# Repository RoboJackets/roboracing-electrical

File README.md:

# RoboRacing Electrical
This is a repository for the RoboJackets' RoboRacing Electrical team.

## rigatoni
Contains current files associated with Rigatoni.

## archive
Contains old files no longer in use on the current robots.

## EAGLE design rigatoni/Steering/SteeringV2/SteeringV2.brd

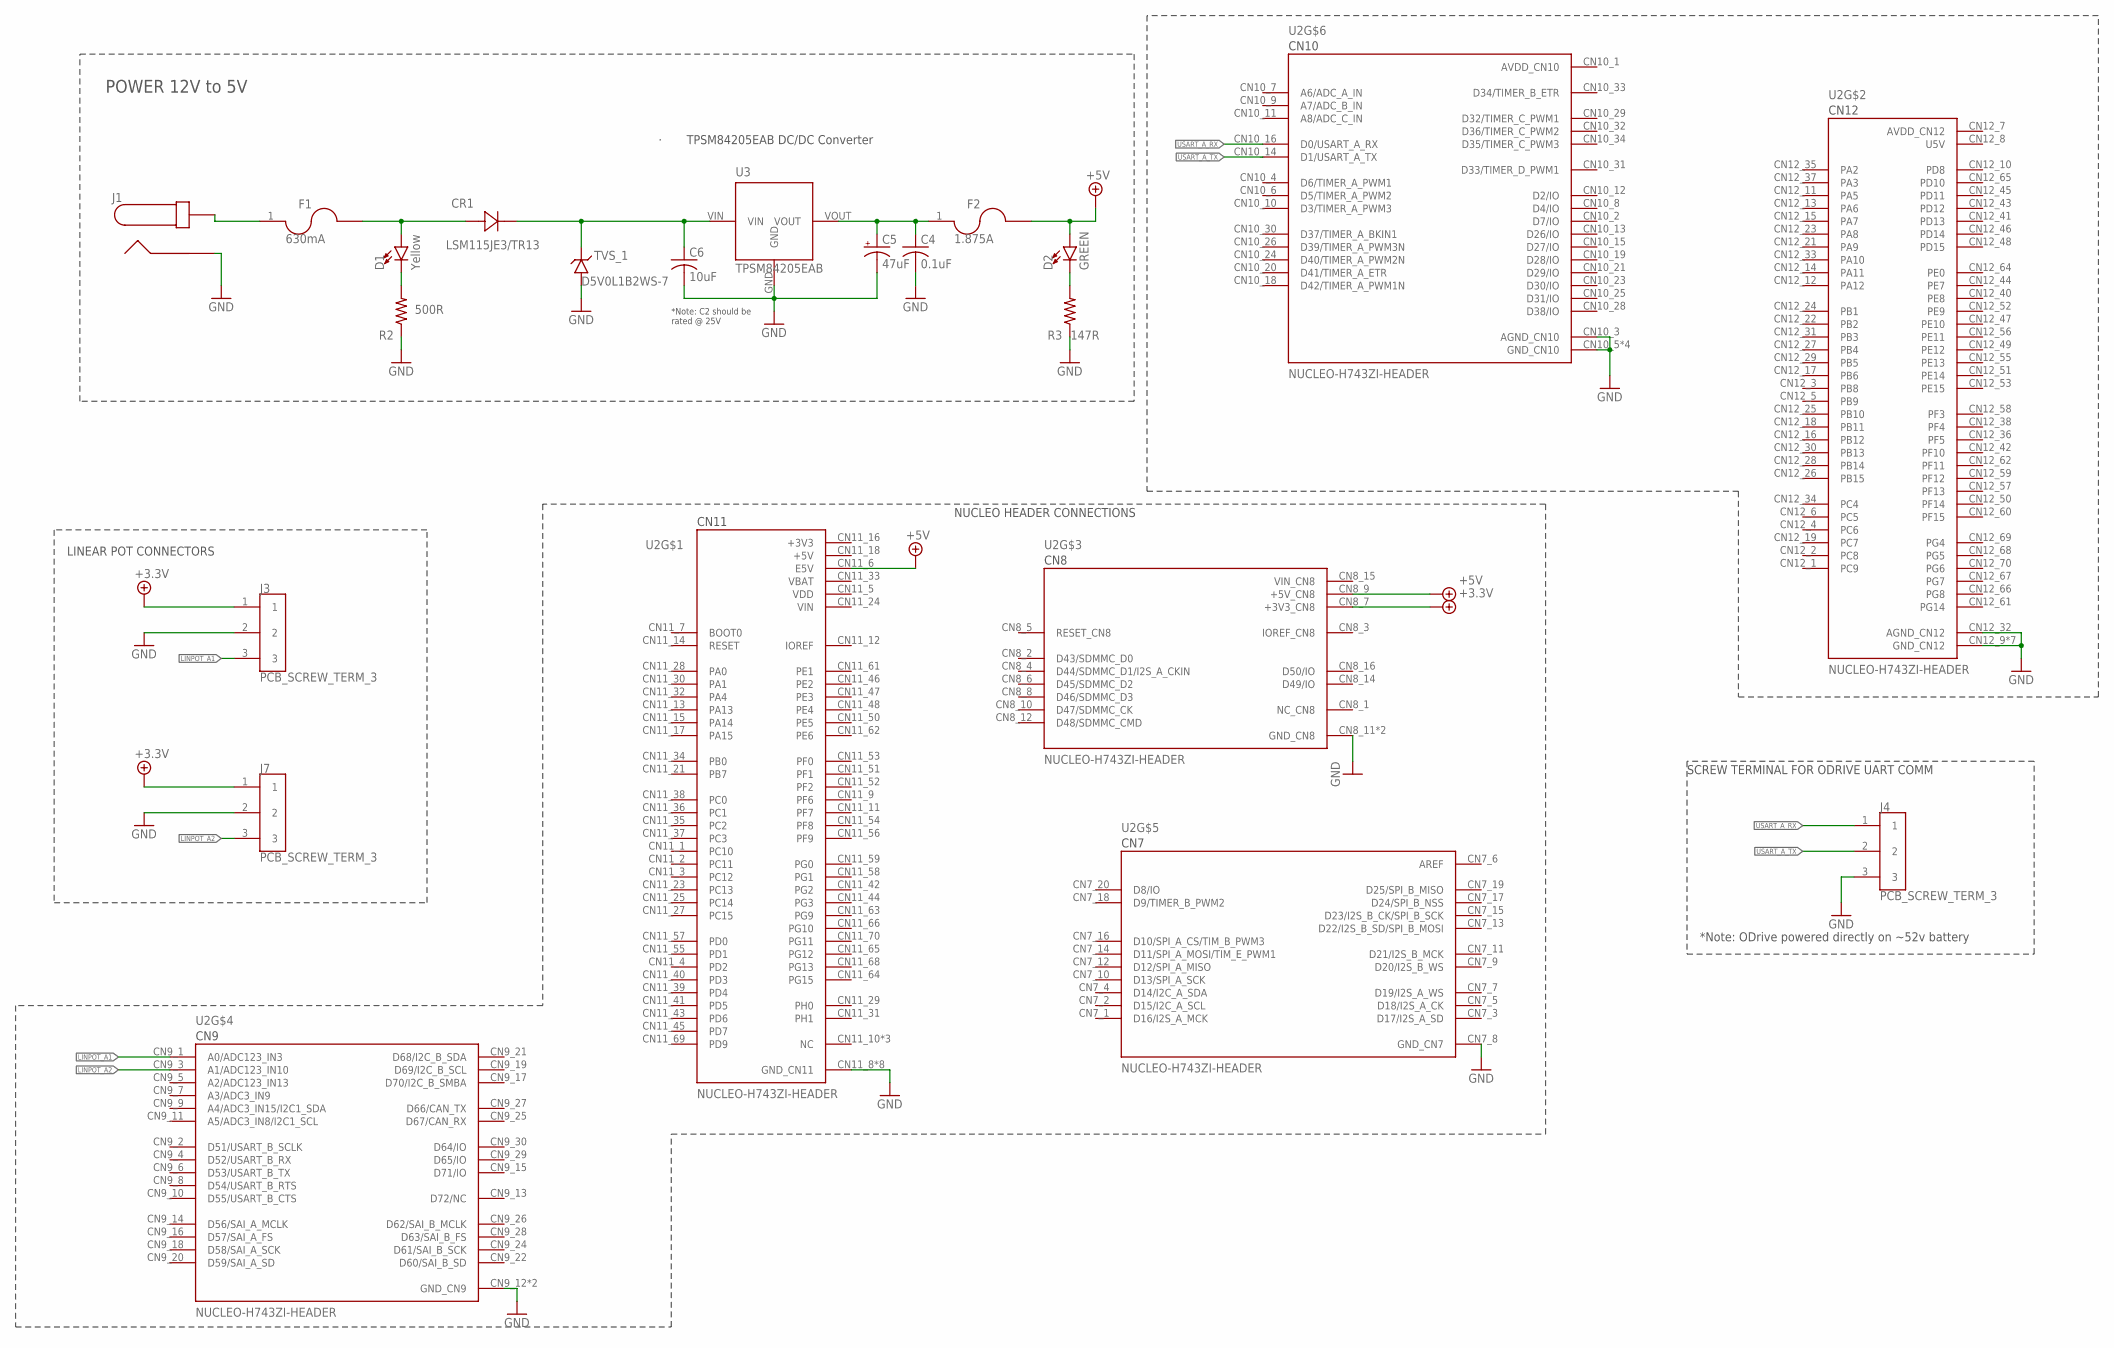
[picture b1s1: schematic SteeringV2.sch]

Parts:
C4: 0.1uF; C0805
C5: 47uF; EIA3528
C6: 10uF; C0805
CR1: LSM115JE3/TR13; DO-214BA_MCH
D1: Yellow; LED-0603
D2: GREEN; LED-1206
F1: 630mA; F0603
F2: 1.875A; F0603
J1: PJ-037A
J3, J4, J7: PCB_SCREW_TERM_3; SCREW_TERMINAL_PCB_CONN_3_POLE
R2: 500R; R0603
R3: 147R; R0603
TVS_1: D5V0L1B2WS-7; SOD-323
U2: NUCLEO-H743ZI-HEADER; MODULE_NUCLEO-H743ZI
U3: TPSM84205EAB

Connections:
5V_MAIN: C4.1, C5.A (+), F2.1, U3.VOUT
+3.3V: J3.1, J7.1, U2.CN8_7 (+3V3_CN8)
+3V3: U2.CN11_16 (+3V3)
+5V: D2.A, F2.2, U2.CN8_9 (+5V_CN8), U2.CN11_6 (E5V), U2.CN11_18 (+5V)
AREF: U2.CN7_6 (AREF)
AVDD_CN10: U2.CN10_1 (AVDD_CN10)
AVDD_CN12: U2.CN12_7 (AVDD_CN12)
GND: C4.2, C5.C (-), C6.2, J1.P$1 (2), J3.2, J4.3, J7.2, R2.1, R3.1, TVS_1.A, U2.CN7_8 (GND_CN7), U2.CN8_11 (GND_CN8), U2.CN8_13 (GND_CN8), U2.CN9_12 (GND_CN9), U2.CN9_23 (GND_CN9), U2.CN10_3 (AGND_CN10), U2.CN10_5 (GND_CN10), U2.CN10_17 (GND_CN10), U2.CN10_22 (GND_CN10), U2.CN10_27 (GND_CN10), U2.CN11_8 (GND_CN11), U2.CN11_19 (GND_CN11), U2.CN11_20 (GND_CN11), U2.CN11_22 (GND_CN11), U2.CN11_49 (GND_CN11), U2.CN11_60 (GND_CN11), U2.CN11_71 (GND_CN11), U2.CN11_72 (GND_CN11), U2.CN12_9 (GND_CN12), U2.CN12_20 (GND_CN12), U2.CN12_32 (AGND_CN12), U2.CN12_39 (GND_CN12), U2.CN12_54 (GND_CN12), U2.CN12_63 (GND_CN12), U2.CN12_71 (GND_CN12), U2.CN12_72 (GND_CN12), U3.GND
LINPOT_A1: J3.3, U2.CN9_1 (A0/ADC123_IN3)
LINPOT_A2: J7.3, U2.CN9_3 (A1/ADC123_IN10)
unnamed: CR1.2, D1.A, F1.2
unnamed: C6.1, CR1.1, TVS_1.C, U3.VIN
unnamed: F1.1, J1.P$2 (1)
unnamed: D1.C, R2.2
unnamed: D2.C, R3.2
U5V: U2.CN12_8 (U5V)
USART_A_RX: J4.1, U2.CN10_16 (D0/USART_A_RX)
USART_A_TX: J4.2, U2.CN10_14 (D1/USART_A_TX)
VBAT: U2.CN11_33 (VBAT)
VDD: U2.CN11_5 (VDD)
VIN: U2.CN11_24 (VIN)
VIN_CN8: U2.CN8_15 (VIN_CN8)

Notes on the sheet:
POWER 12V to 5V
NUCLEO HEADER CONNECTIONS
SCREW TERMINAL FOR ODRIVE UART COMM
LINEAR POT CONNECTORS
*Note: ODrive powered directly on ~52v battery
· TPSM84205EAB DC/DC Converter
*Note: C2 should be rated @ 25V

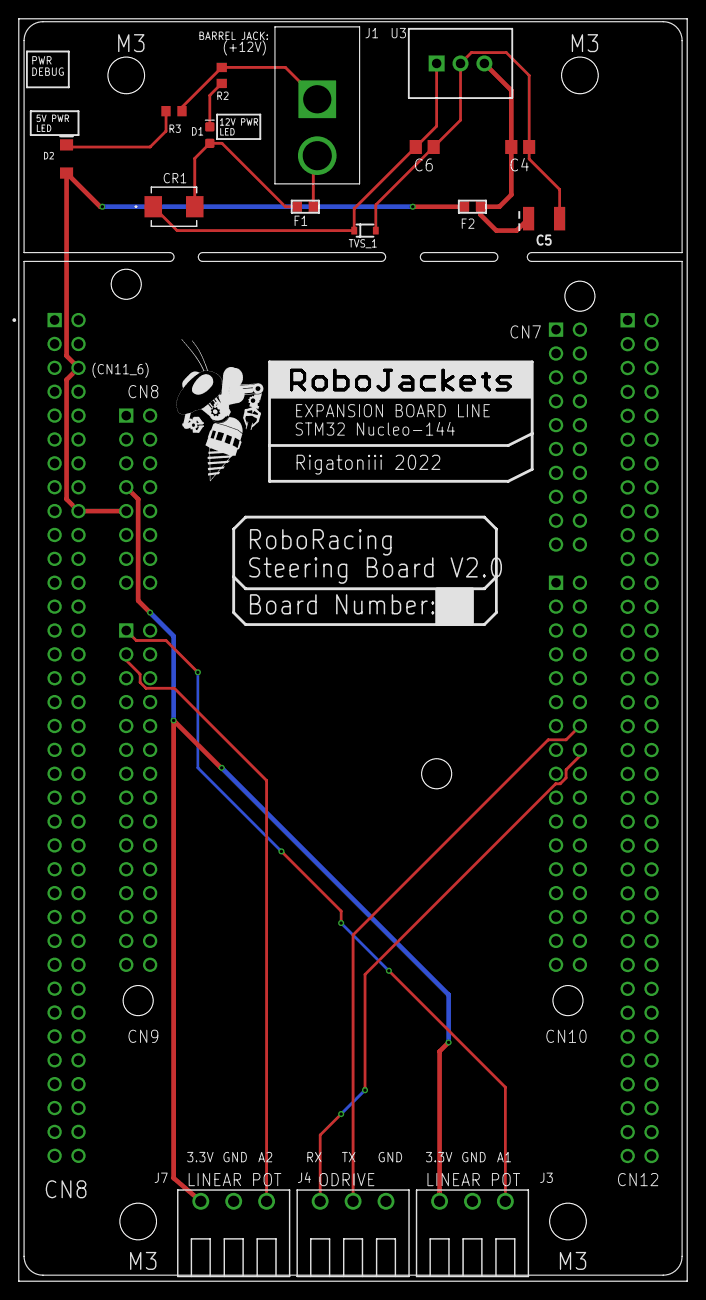
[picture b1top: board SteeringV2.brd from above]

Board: 2 copper layers, 71.1 x 134.3 mm, 23 parts (0 on the bottom side), 13 nets.

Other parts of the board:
U$1: ROBOBUZZ_0.8X
U$2, U$3, U$4, U$5: STANDOFF-HOLE
U$6: ROBOJACKETS

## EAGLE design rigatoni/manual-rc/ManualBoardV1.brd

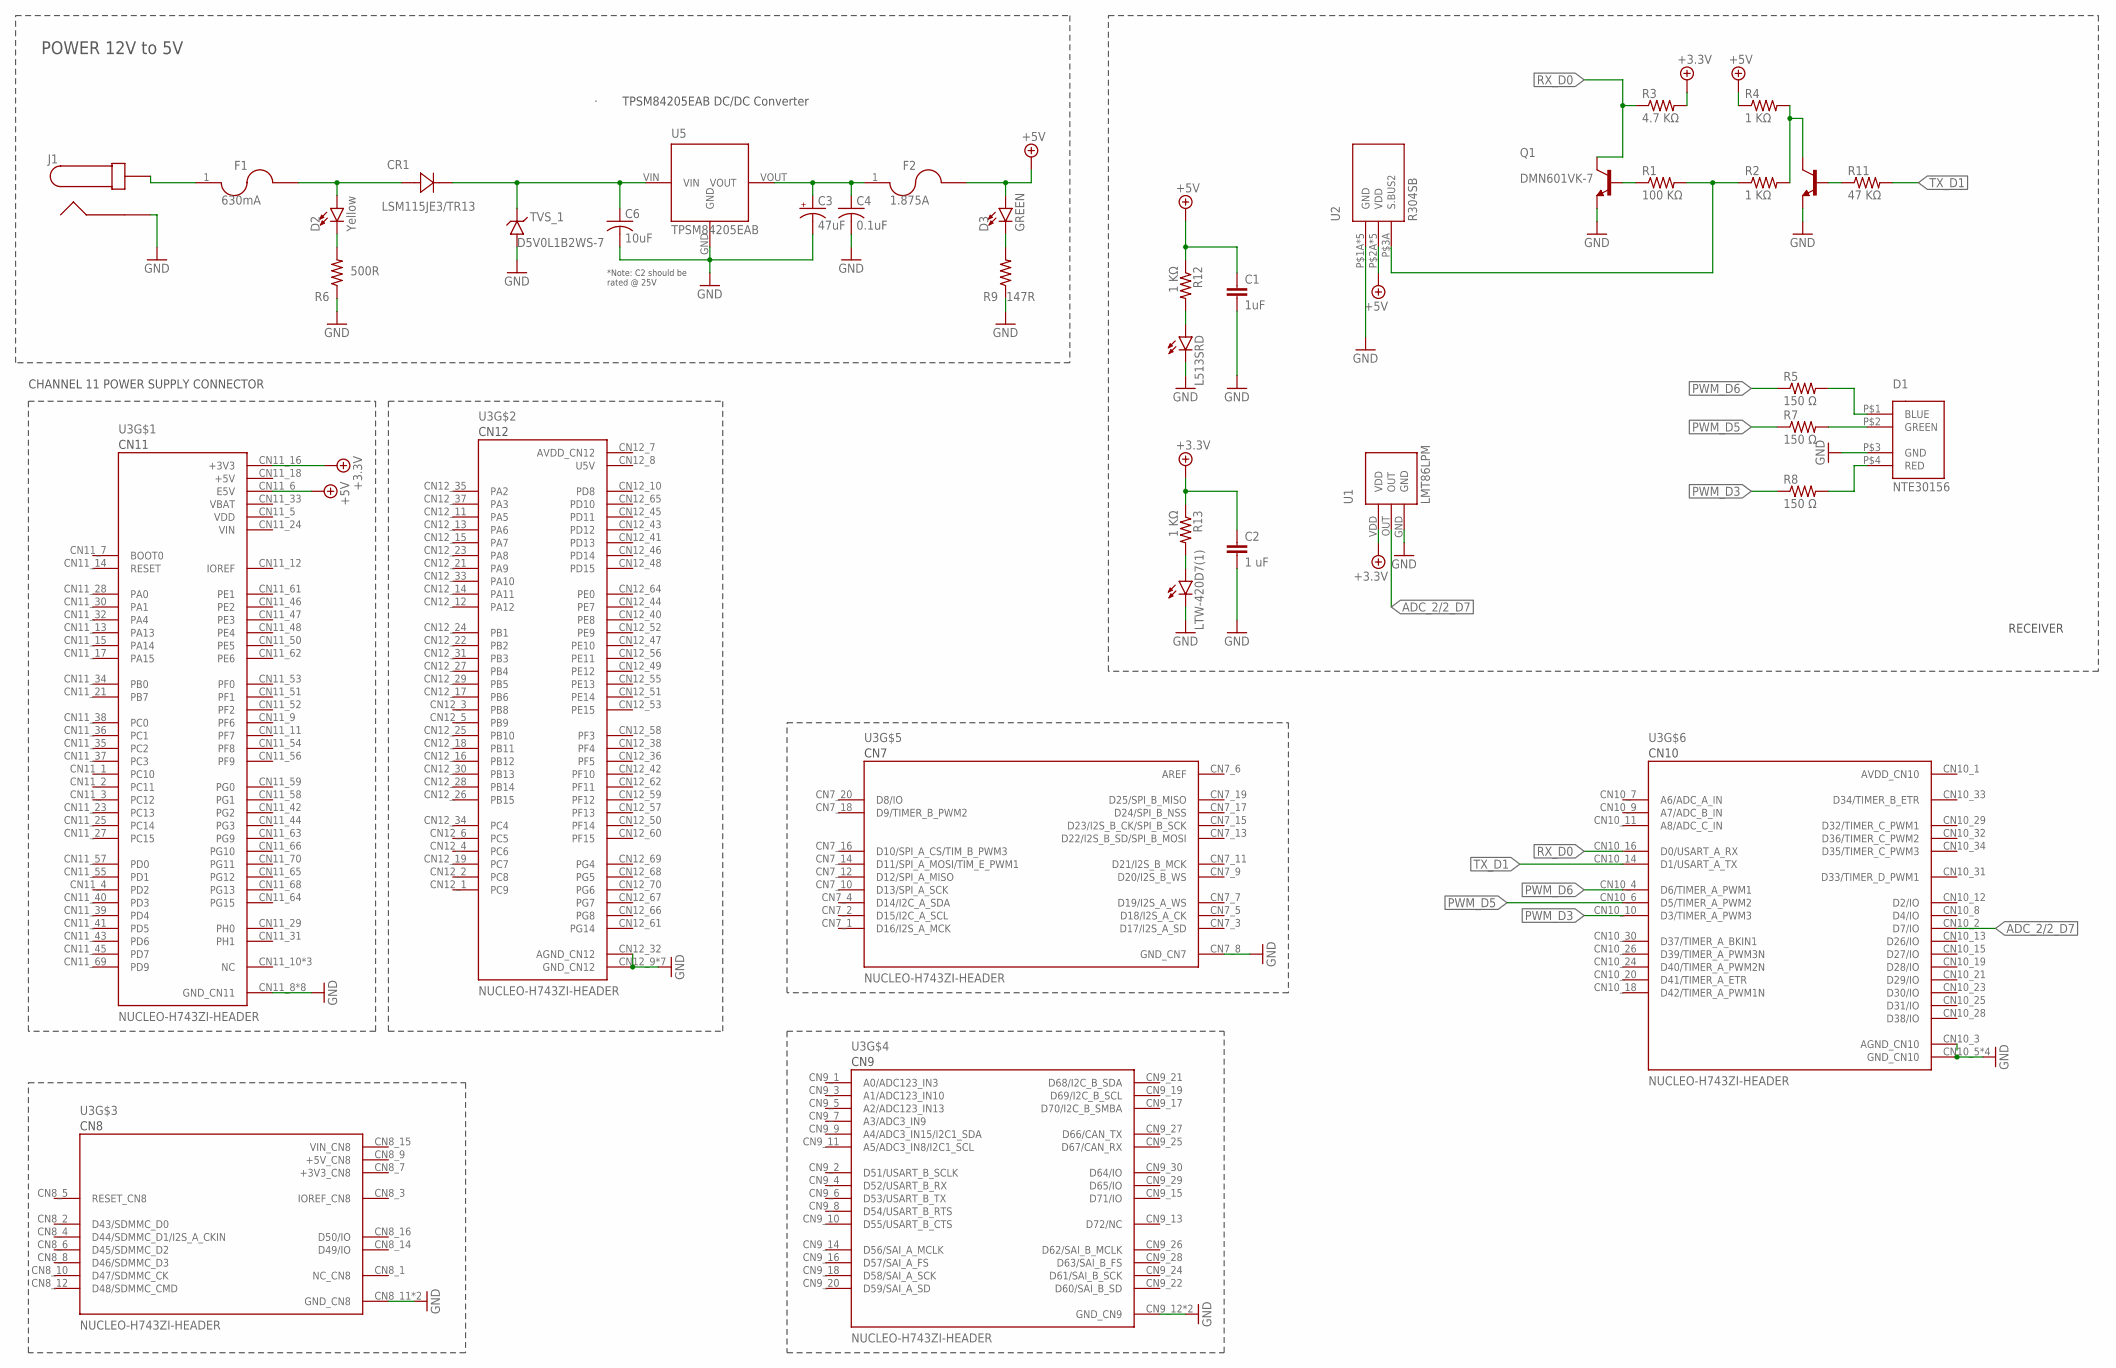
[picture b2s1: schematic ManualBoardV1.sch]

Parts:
C1: 1uF; C2.5-3
C2: 1 uF; C2.5-3
C3: 47uF; EIA3528
C4: 0.1uF; C0805
C6: 10uF; C0805
CR1: LSM115JE3/TR13; DO-214BA_MCH
D1: NTE30156; 4-PIN
D2: Yellow; LED-0603
D3: GREEN; LED-1206
F1: 630mA; F0603
F2: 1.875A; F0603
J1: PJ-037A
L513SRD: LED5MM
LTW-420D7(1): LED5MM
Q1: DMN601VK-7; SOT563
R1: 100 KΩ; 0204/7
R2, R4, R12, R13: 1 KΩ; 0204/7
R3: 4.7 KΩ; 0204/7
R5, R7, R8: 150 Ω; 0204/7
R6: 500R; R0603
R9: 147R; R0603
R11: 47 KΩ; 0204/7
TVS_1: D5V0L1B2WS-7; SOD-323
U1: LMT86LPM; LP
U2: R304SB
U3: NUCLEO-H743ZI-HEADER; MODULE_NUCLEO-HEADER
U5: TPSM84205EAB

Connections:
5V_MAIN: C3.A (+), C4.1, F2.1, U5.VOUT
+3.3V: C2.1, R3.2, R13.1, U1.VDD, U3.CN11_16 (+3V3)
+3V3_CN8: U3.CN8_7 (+3V3_CN8)
+5V: C1.1, D3.A, F2.2, R4.1, R12.1, U2.P$2A (VDD), U2.P$2B (VDD), U2.P$2C (VDD), U2.P$2D (VDD), U2.P$2E (VDD), U3.CN11_6 (E5V), U3.CN11_18 (+5V)
+5V_CN8: U3.CN8_9 (+5V_CN8)
ADC_2/2_D7: U1.OUT, U3.CN10_2 (D7/IO)
AREF: U3.CN7_6 (AREF)
AVDD_CN10: U3.CN10_1 (AVDD_CN10)
AVDD_CN12: U3.CN12_7 (AVDD_CN12)
GND: C1.2, C2.2, C3.C (-), C4.2, C6.2, D1.P$3 (GND), J1.P$1 (2), L513SRD.K (C), LTW-420D7(1).K (C), Q1.D1 (E), Q1.D2 (E1), R6.1, R9.1, TVS_1.A, U1.GND, U2.P$1A (GND), U2.P$1B (GND), U2.P$1C (GND), U2.P$1D (GND), U2.P$1E (GND), U3.CN7_8 (GND_CN7), U3.CN8_11 (GND_CN8), U3.CN8_13 (GND_CN8), U3.CN9_12 (GND_CN9), U3.CN9_23 (GND_CN9), U3.CN10_5 (GND_CN10), U3.CN10_17 (GND_CN10), U3.CN10_22 (GND_CN10), U3.CN10_27 (GND_CN10), U3.CN11_8 (GND_CN11), U3.CN11_19 (GND_CN11), U3.CN11_20 (GND_CN11), U3.CN11_22 (GND_CN11), U3.CN11_49 (GND_CN11), U3.CN11_60 (GND_CN11), U3.CN11_71 (GND_CN11), U3.CN11_72 (GND_CN11), U3.CN12_9 (GND_CN12), U3.CN12_20 (GND_CN12), U3.CN12_32 (AGND_CN12), U3.CN12_39 (GND_CN12), U3.CN12_54 (GND_CN12), U3.CN12_63 (GND_CN12), U3.CN12_71 (GND_CN12), U3.CN12_72 (GND_CN12), U5.GND
unnamed: Q1.G1 (B), R1.1
unnamed: Q1.S2 (C1), R2.2, R4.2
unnamed: C6.1, CR1.1, TVS_1.C, U5.VIN
unnamed: F1.1, J1.P$2 (1)
unnamed: D1.P$1 (BLUE), R5.2
unnamed: R1.2, R2.1, U2.P$3A (S.BUS2)
unnamed: D1.P$2 (GREEN), R7.2
unnamed: CR1.2, D2.A, F1.2
unnamed: D1.P$4 (RED), R8.2
unnamed: D2.C, R6.2
unnamed: D3.C, R9.2
unnamed: Q1.G2 (B1), R11.1
unnamed: L513SRD.A, R12.2
unnamed: LTW-420D7(1).A, R13.2
PWM_D3: R8.1, U3.CN10_10 (D3/TIMER_A_PWM3)
PWM_D5: R7.1, U3.CN10_6 (D5/TIMER_A_PWM2)
PWM_D6: R5.1, U3.CN10_4 (D6/TIMER_A_PWM1)
RX_D0: Q1.S1 (C), R3.1, U3.CN10_16 (D0/USART_A_RX)
TX_D1: R11.2, U3.CN10_14 (D1/USART_A_TX)
U5V: U3.CN12_8 (U5V)
VBAT: U3.CN11_33 (VBAT)
VDD: U3.CN11_5 (VDD)
VIN: U3.CN11_24 (VIN)
VIN_CN8: U3.CN8_15 (VIN_CN8)

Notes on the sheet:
CHANNEL 11 POWER SUPPLY CONNECTOR
RECEIVER
POWER 12V to 5V
· TPSM84205EAB DC/DC Converter
*Note: C2 should be rated @ 25V

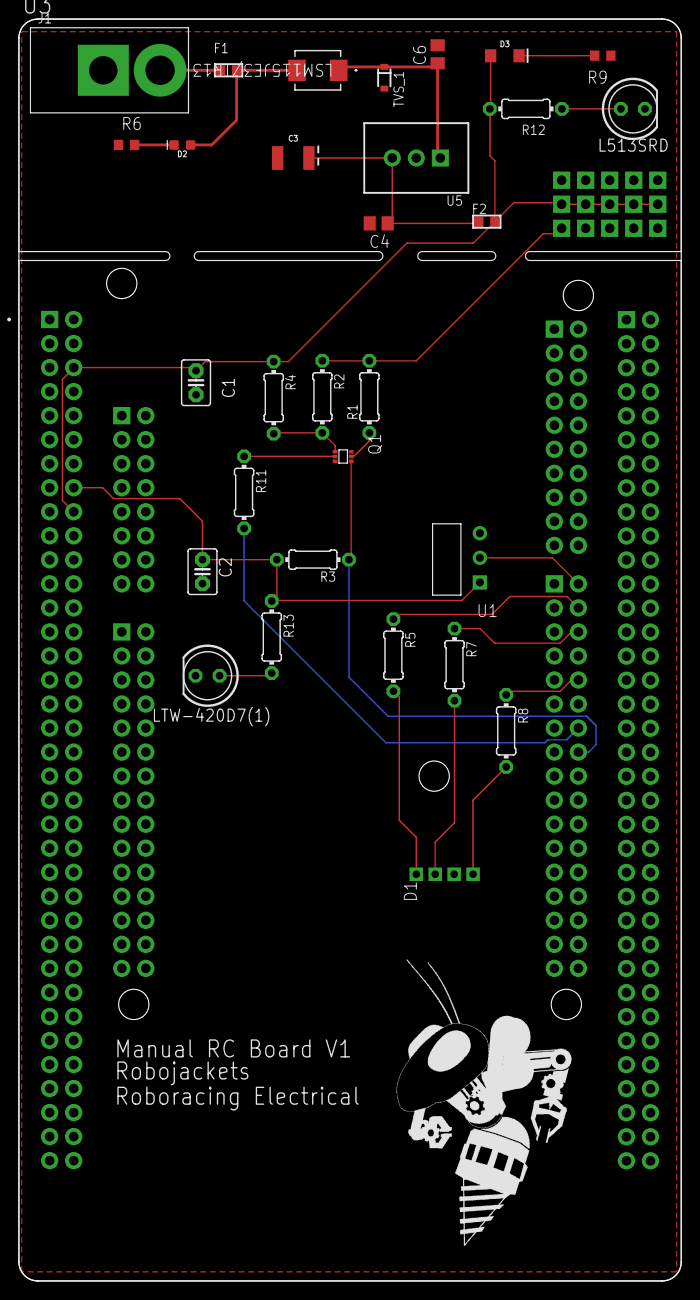
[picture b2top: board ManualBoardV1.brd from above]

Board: 2 copper layers, 70.0 x 133.4 mm, 33 parts (0 on the bottom side), 24 nets.

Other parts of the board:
U$1: ROBOBUZZ_1.4X

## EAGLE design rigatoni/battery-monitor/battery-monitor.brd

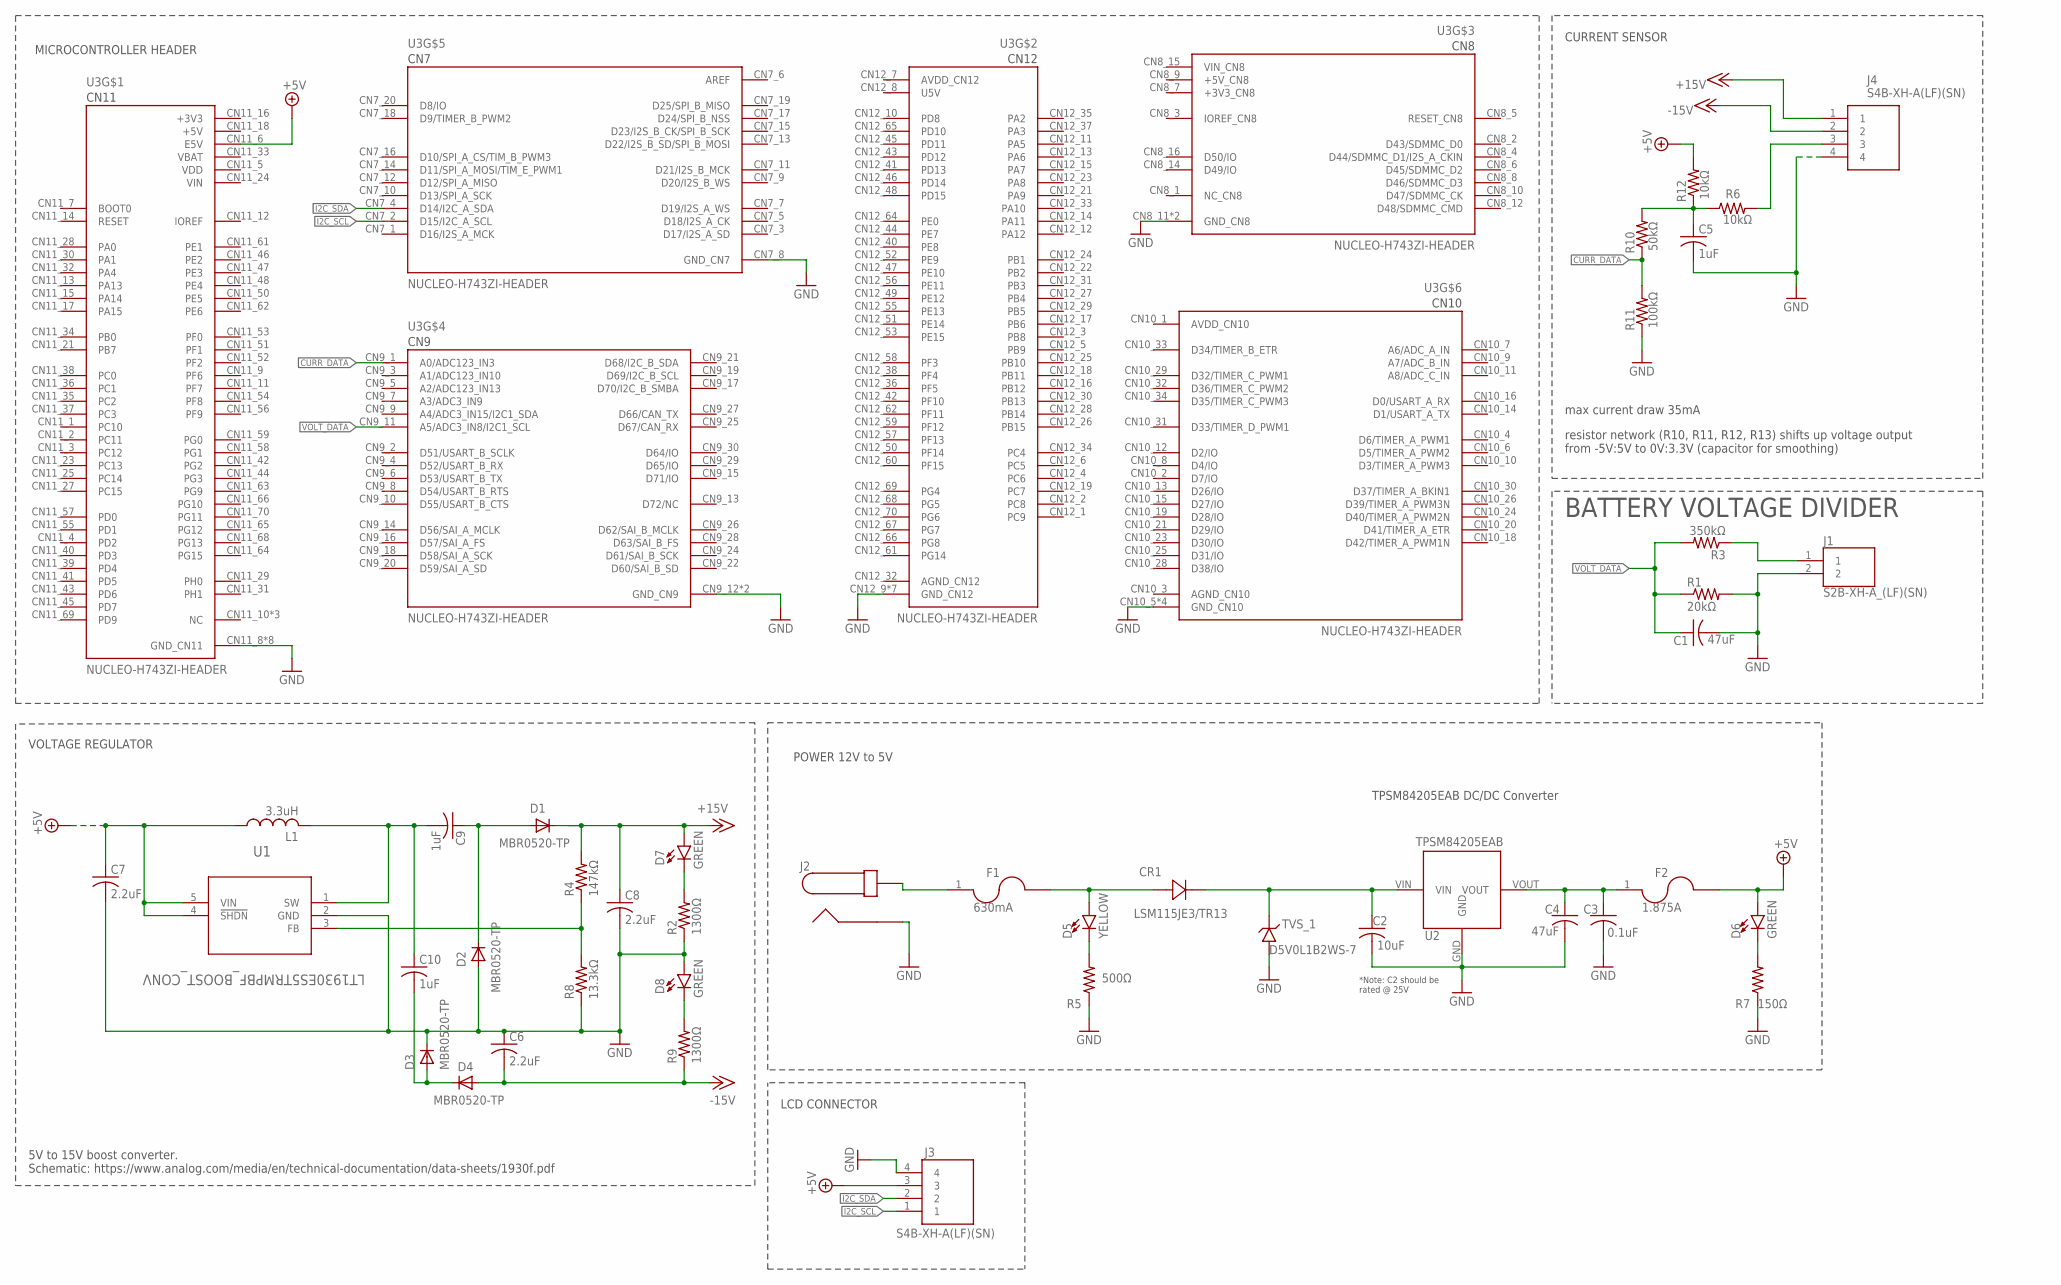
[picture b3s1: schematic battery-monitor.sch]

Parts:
C1, C4: 47uF; C0603
C2: 10uF; C0603
C3: 0.1uF; C0603
C5, C9, C10: 1uF; C0603
C6, C8: 2.2uF; C1206
C7: 2.2uF; C0805
CR1: LSM115JE3/TR13; DO-214BA_MCH
D1, D2, D3, D4: MBR0520-TP; SOD123
D5: YELLOW; LED-0603
D6: GREEN; LED-1206
D7, D8: GREEN; LED-0603
F1: 630mA; F0603
F2: 1.875A; F0603
J1: S2B-XH-A_(LF)(SN); SHDR2W80P0X250_1X2_740X1150X61
J2: PJ-037A
J3, J4: S4B-XH-A(LF)(SN); SHDR4W64P0X250_1X4_1240X1155X7
L1: 3.3uH; L3225M
R1: 20kΩ; R0603
R2, R9: 1300Ω; R0603
R3: 350kΩ; R0603
R4: 147kΩ; R0603
R5: 500Ω; R0603
R6, R12: 10kΩ; R0603
R7: 150Ω; R0603
R8: 13.3kΩ; R0603
R10: 50kΩ; R0603
R11: 100kΩ; R0603
TVS_1: D5V0L1B2WS-7; SOD-323
U1: LT1930ES5TRMPBF_BOOST_CONV; SOT-5_S
U2: TPSM84205EAB
U3: NUCLEO-H743ZI-HEADER; MODULE_NUCLEO-HEADER

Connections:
5V_MAIN: C3.1, C4.1, F2.1, U2.VOUT
+3V3: U3.CN11_16 (+3V3)
+3V3_CN8: U3.CN8_7 (+3V3_CN8)
+5V: C7.1, D6.A, F2.2, J3.3, L1.1, R12.2, U1.4 (!SHDN), U1.5 (VIN), U3.CN11_6 (E5V), U3.CN11_18 (+5V)
+5V_CN8: U3.CN8_9 (+5V_CN8)
+15V: C8.1, D1.C, D7.A, J4.1, R4.2
-15V: C6.2, D4.A, J4.2, R9.1
AGND_CN10: U3.CN10_3 (AGND_CN10)
AGND_CN12: U3.CN12_32 (AGND_CN12)
AREF: U3.CN7_6 (AREF)
AVDD_CN10: U3.CN10_1 (AVDD_CN10)
AVDD_CN12: U3.CN12_7 (AVDD_CN12)
CURR_DATA: R10.1, R11.2, U3.CN9_1 (A0/ADC123_IN3)
CURR_RAW: J4.3, R6.2
GND: C1.2, C2.2, C3.2, C4.2, C5.2, C6.1, C7.2, C8.2, D2.A, D3.C, D8.A, J1.2, J2.P$1 (2), J3.4, J4.4, R1.2, R2.1, R5.1, R7.1, R8.1, R11.1, TVS_1.A, U1.2 (GND), U2.GND, U3.CN7_8 (GND_CN7), U3.CN8_11 (GND_CN8), U3.CN8_13 (GND_CN8), U3.CN9_12 (GND_CN9), U3.CN9_23 (GND_CN9), U3.CN10_5 (GND_CN10), U3.CN10_17 (GND_CN10), U3.CN10_22 (GND_CN10), U3.CN10_27 (GND_CN10), U3.CN11_8 (GND_CN11), U3.CN11_19 (GND_CN11), U3.CN11_20 (GND_CN11), U3.CN11_22 (GND_CN11), U3.CN11_49 (GND_CN11), U3.CN11_60 (GND_CN11), U3.CN11_71 (GND_CN11), U3.CN11_72 (GND_CN11), U3.CN12_9 (GND_CN12), U3.CN12_20 (GND_CN12), U3.CN12_39 (GND_CN12), U3.CN12_54 (GND_CN12), U3.CN12_63 (GND_CN12), U3.CN12_71 (GND_CN12), U3.CN12_72 (GND_CN12)
I2C_SCL: J3.1, U3.CN7_2 (D15/I2C_A_SCL)
I2C_SDA: J3.2, U3.CN7_4 (D14/I2C_A_SDA)
unnamed: J1.1, R3.1
unnamed: CR1.2, D5.A, F1.2
unnamed: C2.1, CR1.1, TVS_1.C, U2.VIN
unnamed: F1.1, J2.P$2 (1)
unnamed: R4.1, R8.2, U1.3 (FB)
unnamed: C9.2, C10.1, L1.2, U1.1 (SW)
unnamed: D5.C, R5.2
unnamed: C10.2, D3.A, D4.C
unnamed: D6.C, R7.2
unnamed: C5.1, R6.1, R10.2, R12.1
unnamed: D7.C, R2.2
unnamed: C9.1, D1.A, D2.C
unnamed: D8.C, R9.2
U5V: U3.CN12_8 (U5V)
VBAT: U3.CN11_33 (VBAT)
VDD: U3.CN11_5 (VDD)
VIN: U3.CN11_24 (VIN)
VIN_CN8: U3.CN8_15 (VIN_CN8)
VOLT_DATA: C1.1, R1.1, R3.2, U3.CN9_11 (A5/ADC3_IN8/I2C1_SCL)

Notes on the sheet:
CURRENT SENSOR
max current draw 35mA
resistor network (R10, R11, R12, R13) shifts up voltage output from -5V:5V to 0V:3.3V (capacitor for smoothing)
VOLTAGE REGULATOR
5V to 15V boost converter. Schematic: https://www.analog.com/media/en/technical-documentation/data-sheets/1930f.pdf
BATTERY VOLTAGE DIVIDER
MICROCONTROLLER HEADER
LCD CONNECTOR
POWER 12V to 5V
TPSM84205EAB DC/DC Converter
*Note: C2 should be rated @ 25V

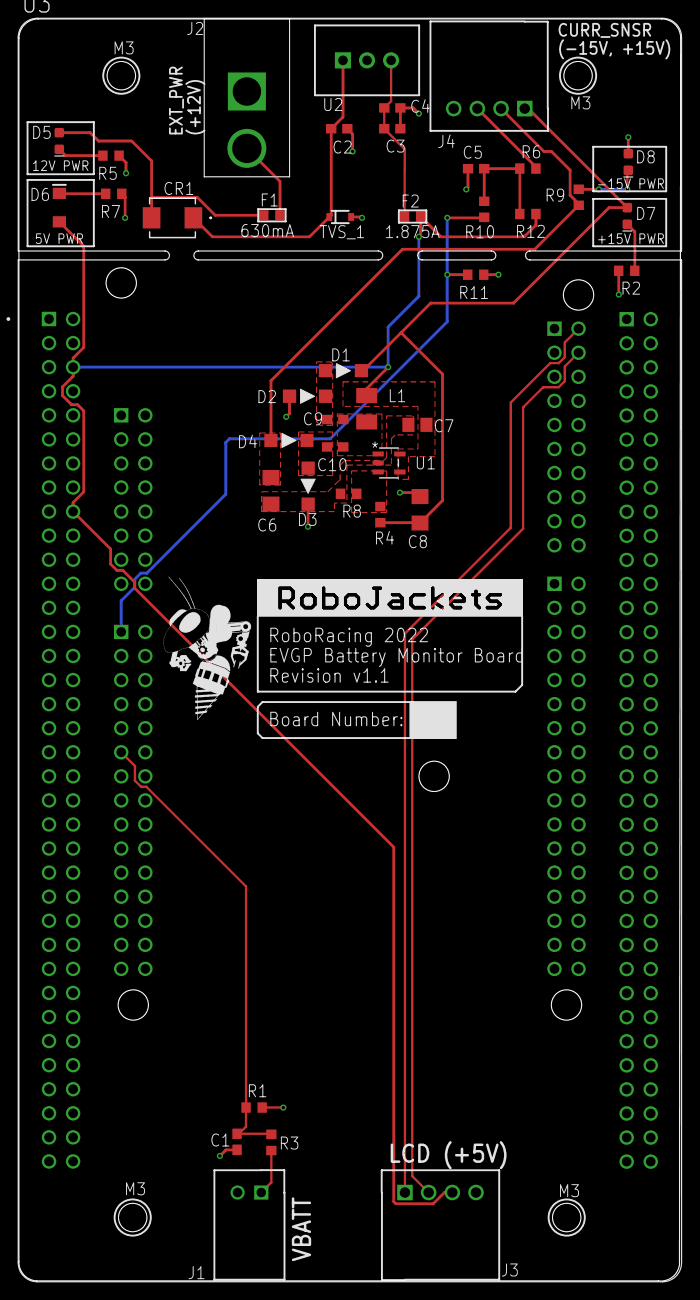
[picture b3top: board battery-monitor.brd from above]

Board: 2 copper layers, 69.8 x 133.2 mm, 45 parts (1 on the bottom side), 23 nets.

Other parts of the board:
U$1, U$3: ROBOBUZZ_0.8X
U$2: ROBOJACKETS

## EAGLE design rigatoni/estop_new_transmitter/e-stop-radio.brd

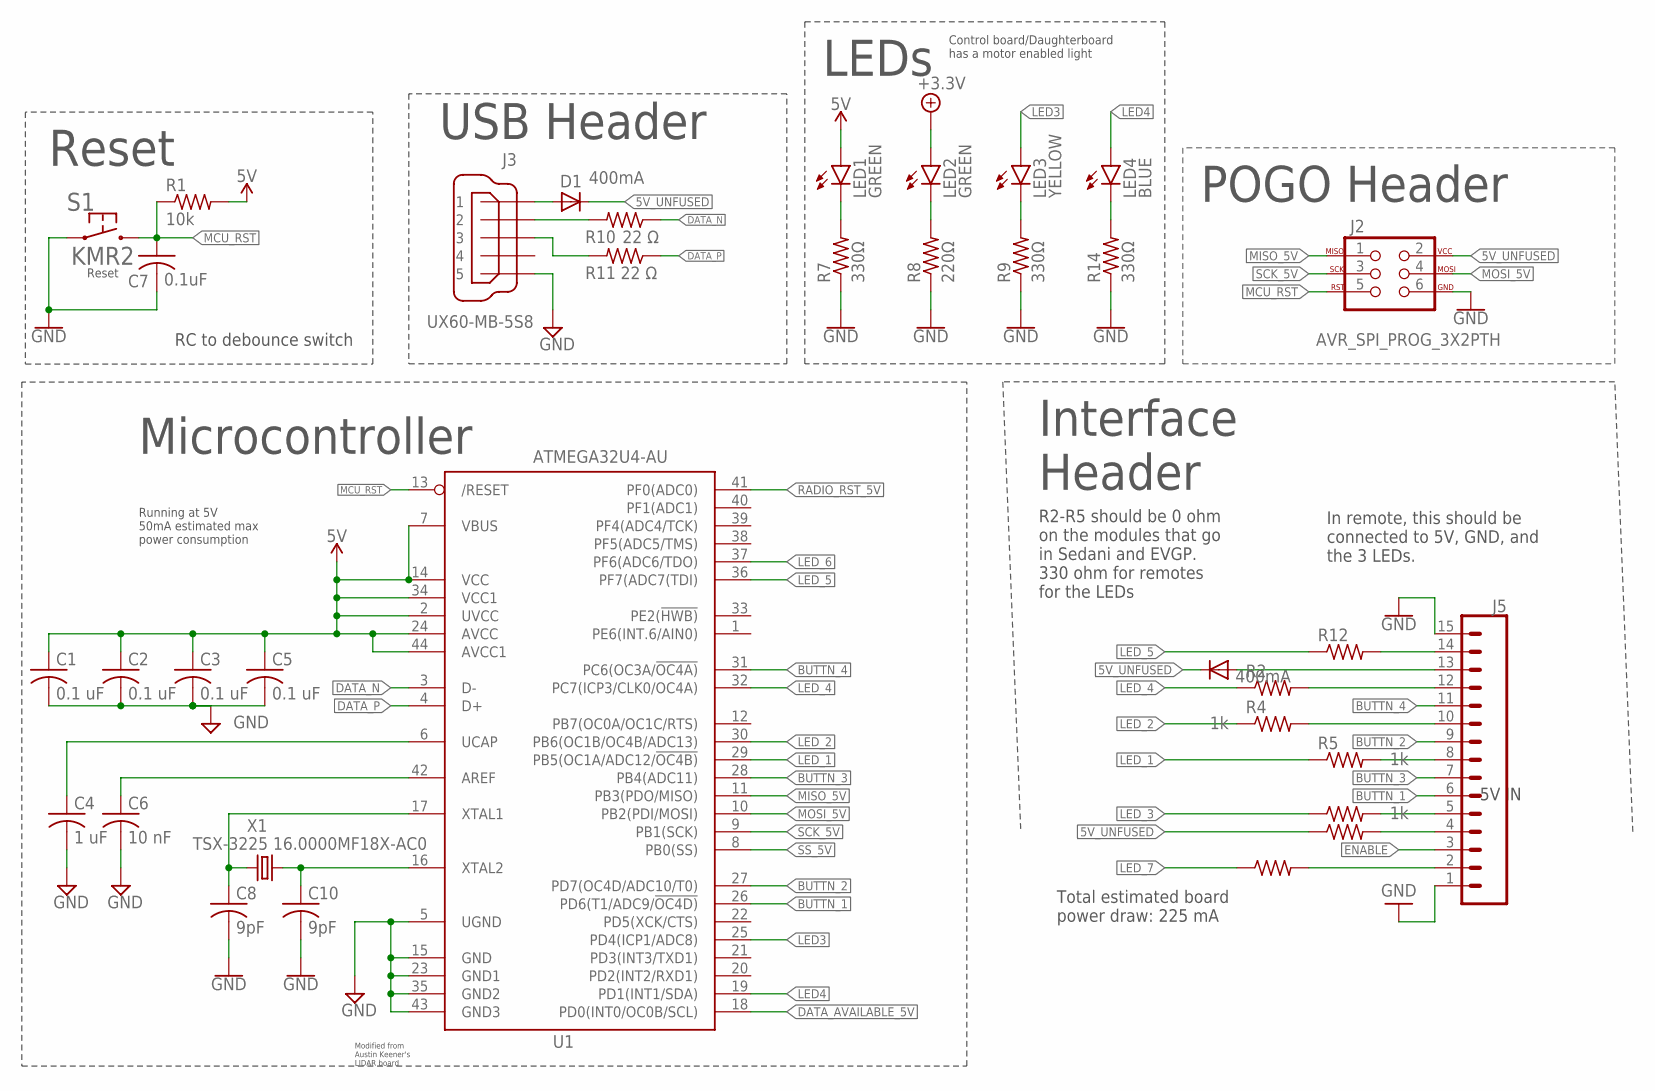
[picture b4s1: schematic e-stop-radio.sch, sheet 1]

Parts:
C1, C2, C3, C5: 0.1 uF; C0603
C4: 1 uF; C0603
C6: 10 nF; C0603
C7: 0.1uF; C0603
C8, C10: 9pF; C0603
D1, D4: 400mA; SOD323-R
J2: AVR_SPI_PROG_3X2PTH; 2X3
J3: UX60-MB-5S8
J5: CONN_15; 1X15
LED1, LED2: GREEN; CHIP-LED0603
LED3: YELLOW; CHIP-LED0603
LED4: BLUE; CHIP-LED0603
R1: 10k; R0603
R2, R12, R17, R18: 330; R0603
R3\, R4, R5: 1k; R0603
R7, R9, R14: 330Ω; R0603
R8: 220Ω; R0603
R10, R11: 22 Ω; R0603
S1: KMR2
U1: ATMEGA32U4-AU; TQFP44
X1: TSX-3225 16.0000MF18X-AC0; XTAL-3.2X2.5

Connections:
5V: C1.1, C2.1, C3.1, C5.1, LED1.A, R1.2, U1.2 (UVCC), U1.7 (VBUS), U1.14 (VCC), U1.24 (AVCC), U1.34 (VCC1), U1.44 (AVCC1); also elsewhere on the board
5V_UNFUSED: D1.C, D4.C, J2.2, R17.1; also elsewhere on the board
+3.3V: LED2.A; also elsewhere on the board
AREF: C6.1, U1.42 (AREF)
BUTTN_1: J5.6, U1.26 (PD6(T1/ADC9/!OC4D))
BUTTN_2: J5.9, U1.27 (PD7(OC4D/ADC10/T0))
BUTTN_3: J5.7, U1.28 (PB4(ADC11))
BUTTN_4: J5.11, U1.31 (PC6(OC3A/!OC4A))
DATA_AVAILABLE_5V: U1.18 (PD0(INT0/OC0B/SCL)); also elsewhere on the board
DATA_N: R10.1, U1.3 (D-)
DATA_P: R11.1, U1.4 (D+)
DIO_4_R: J5.8, R5.2
DIO_5_R: J5.10, R4.2
DIO_6_R: J5.5, R3\.2
DIO_7_R: J5.12, R2.2
DIO_7_R1: J5.14, R12.2
DIO_7_R2: J5.4, R17.2
DIO_7_R3: J5.2, R18.2
ENABLE: J5.3; also elsewhere on the board
GND: C1.2, C2.2, C3.2, C4.2, C5.2, C6.2, C7.2, C8.2, C10.2, J2.6, J3.5, J5.15, R7.1, R8.1, R9.1, R14.1, S1.1.1 (1), S1.1.2 (1), U1.5 (UGND), U1.15 (GND), U1.23 (GND1), U1.35 (GND2), U1.43 (GND3); also elsewhere on the board
H4: D4.A, J5.13
LED3: LED3.A, U1.25 (PD4(ICP1/ADC8))
LED4: LED4.A, U1.19 (PD1(INT1/SDA))
LED_1: R5.1, U1.29 (PB5(OC1A/ADC12/!OC4B))
LED_2: R4.1, U1.30 (PB6(OC1B/OC4B/ADC13))
LED_3: R3\.1
LED_4: R2.1, U1.32 (PC7(ICP3/CLK0/OC4A))
LED_5: R12.1, U1.36 (PF7(ADC7(TDI))
LED_6: U1.37 (PF6(ADC6/TDO))
LED_7: R18.1; also elsewhere on the board
MCU_RST: C7.1, J2.5, R1.1, S1.2.1 (2), S1.2.2 (2), U1.13 (/RESET)
MISO_5V: J2.1, U1.11 (PB3(PDO/MISO)); also elsewhere on the board
MOSI_5V: J2.4, U1.10 (PB2(PDI/MOSI)); also elsewhere on the board
unnamed: LED3.C, R9.2
unnamed: LED1.C, R7.2
unnamed: LED2.C, R8.2
unnamed: J3.2, R10.2
unnamed: LED4.C, R14.2
unnamed: D1.A, J3.1
unnamed: J3.3, R11.2
RADIO_RST_5V: U1.41 (PF0(ADC0)); also elsewhere on the board
SCK_5V: J2.3, U1.9 (PB1(SCK)); also elsewhere on the board
SS_5V: U1.8 (PB0(SS)); also elsewhere on the board
UCAP: C4.1, U1.6 (UCAP)
XTAL1: C8.1, U1.17 (XTAL1), X1.1
XTAL2: C10.1, U1.16 (XTAL2), X1.3 (2)

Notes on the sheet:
Modified from Austin Keener's LIDAR board
5V IN
Interface Header
POGO Header
RC to debounce switch
Reset
Control board/Daughterboard has a motor enabled light
LEDs
Running at 5V 50mA estimated max power consumption
In remote, this should be connected to 5V, GND, and the 3 LEDs.
R2-R5 should be 0 ohm on the modules that go in Sedani and EVGP. 330 ohm for remotes for the LEDs
Microcontroller
USB Header
Total estimated board power draw: 225 mA

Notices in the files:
parts and their libraries:
SparkFun-Connectors: Licensing: Creative Commons ShareAlike 4.0 International - https://creativecommons.org/licenses/by-sa/4.0
COPYRIGHT: Copyright (C) 2022 Ultra Librarian. All rights reserved.
